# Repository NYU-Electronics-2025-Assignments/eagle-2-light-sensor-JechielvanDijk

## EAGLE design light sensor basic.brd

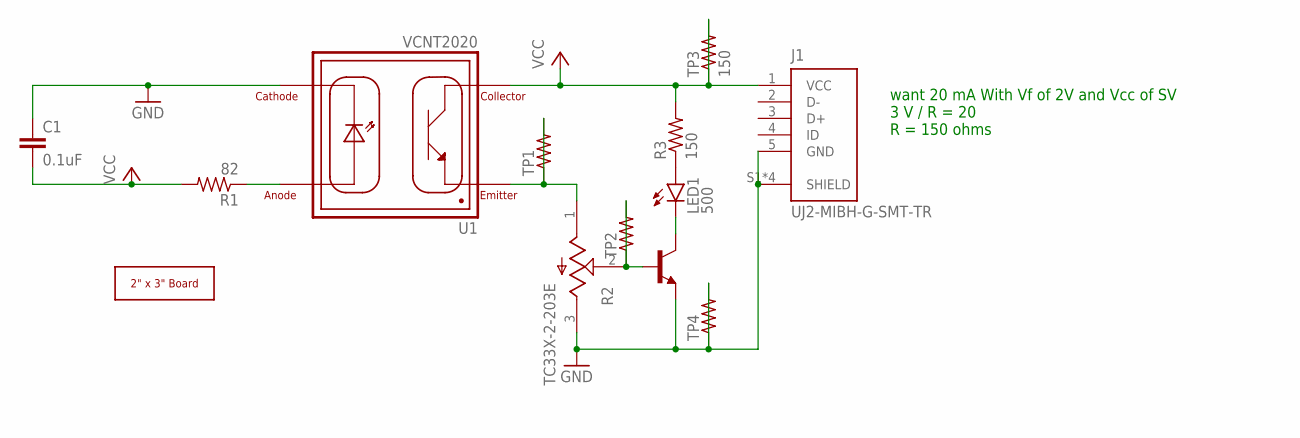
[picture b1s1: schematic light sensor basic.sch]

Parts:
C1: 0.1uF; C1206
J1: UJ2-MIBH-G-SMT-TR; CUI_UJ2-MIBH-G-SMT-TR
LED1: 500; SML0805
R1: 82; R1206
R2: TC33X-2-203E; TRIM_TC33X-2-203E
R3: 150; R0805
T1: -NPN-SOT23-EBC; SOT23-EBC
TP1, TP2, TP4: R-US_R1206; R1206
TP3: 150; R0805
U1: VCNT2020; XDCR_VCNT2020
U$1: 2X3_BOARD_V2

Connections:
GND: C1.1, J1.5 (GND), J1.S1 (SHIELD), J1.S2 (SHIELD), J1.S3 (SHIELD), J1.S4 (SHIELD), R2.3 (CW), T1.E, TP4.1, TP4.2, U1.4 (CATHODE)
unnamed: R1.1, U1.3 (ANODE)
unnamed: R2.2 (W), T1.B, TP2.1, TP2.2
unnamed: LED1.C, T1.C
unnamed: R2.1 (CCW), TP1.1, TP1.2, U1.1 (EMITTER)
unnamed: LED1.A, R3.1
VCC: C1.2, J1.1 (VCC), R1.2, R3.2, TP3.1, TP3.2, U1.2 (COLLECTOR)

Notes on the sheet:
want 20 mA With Vf of 2V and Vcc of SV 3 V / R = 20 R = 150 ohms

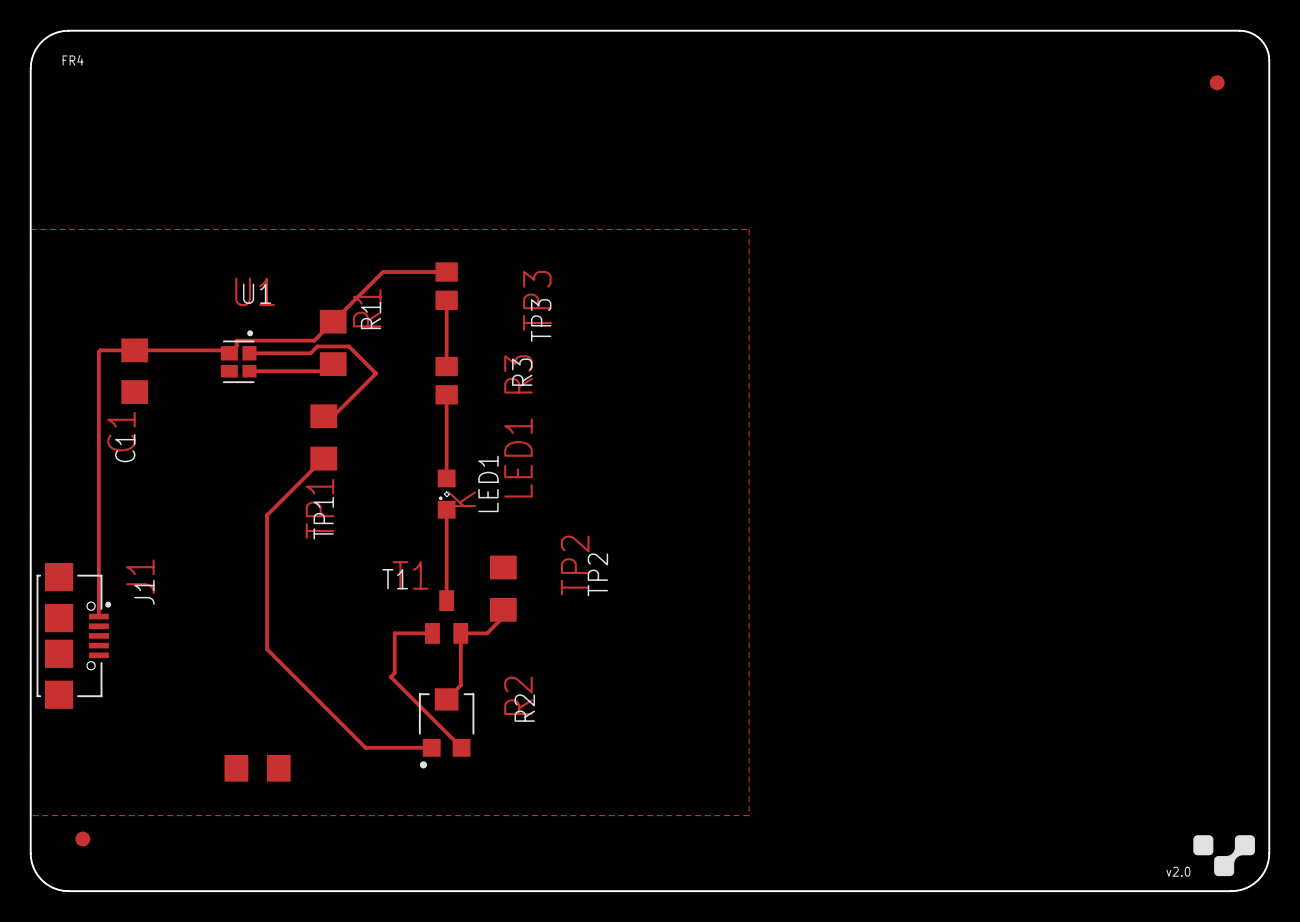
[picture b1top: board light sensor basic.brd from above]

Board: 2 copper layers, 83.2 x 57.8 mm, 13 parts (0 on the bottom side), 7 nets.

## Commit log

2025-02-28 eagle assignment 2
